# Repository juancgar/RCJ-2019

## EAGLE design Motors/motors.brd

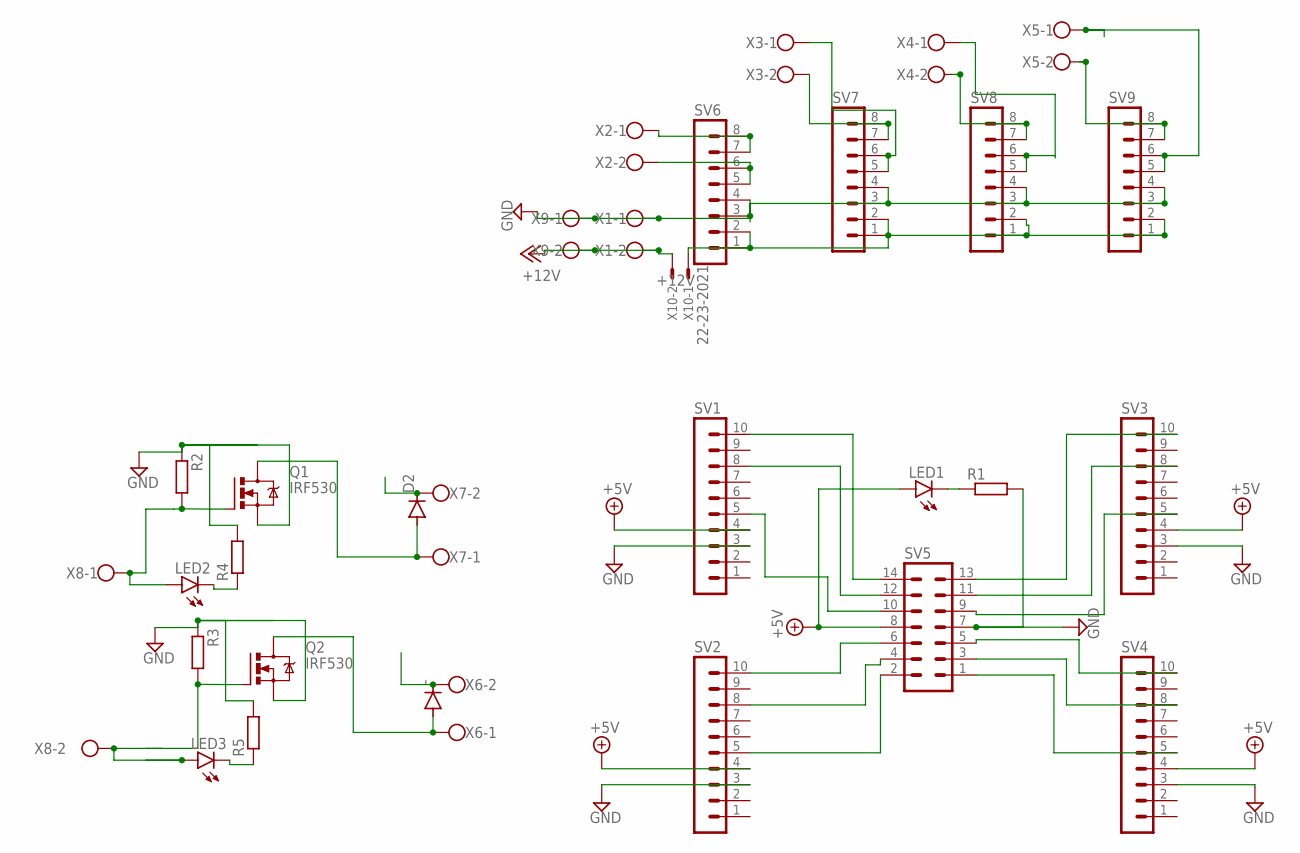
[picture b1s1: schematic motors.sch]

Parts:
-: DIODE-DO41-7.6; DO41-7.6
D2: DIODE-DO41-7.6; DO41-7.6
LED1, LED2, LED3: LED5MM
Q1, Q2: IRF530; TO220BV
R1, R2, R3, R4, R5: R-EU_0207/7; 0207/7
SV1, SV2, SV3, SV4: MA10-1
SV5: MA07-2
SV6, SV7, SV8, SV9: MA08-1
X1, X2, X3, X4, X5, X6, X7, X8, X9: W237-102
X10: 22-23-2021

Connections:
+5V: LED1.A, SV1.4, SV2.4, SV3.4, SV4.4, SV5.8
+12V: X1.2, X9.2, X10.2
GND: Q1.S, Q2.S, R1.2, R2.1, R3.1, R4.2, R5.2, SV1.3, SV2.3, SV3.3, SV4.3, SV5.7, SV6.3, SV6.4, SV7.3, SV7.4, SV8.3, SV8.4, SV9.3, SV9.4, X1.1, X9.1
unnamed: SV3.10, SV5.13
unnamed: SV3.8, SV5.11
unnamed: SV3.5, SV5.9
unnamed: SV4.10, SV5.5
unnamed: SV4.8, SV5.3
unnamed: SV4.5, SV5.1
unnamed: SV2.5, SV5.2
unnamed: SV2.8, SV5.4
unnamed: SV2.10, SV5.6
unnamed: SV1.5, SV5.10
unnamed: SV1.8, SV5.12
unnamed: SV1.10, SV5.14
unnamed: LED1.K (C), R1.1
unnamed: LED2.K (C), R4.1
unnamed: LED3.A, Q2.G, R3.2, X8.2
unnamed: D2.A, Q1.D, X7.1
unnamed: LED3.K (C), R5.1
unnamed: -.A, Q2.D, X6.1
unnamed: SV9.7, SV9.8, X5.2
unnamed: -.C, D2.C, SV6.1, SV6.2, SV7.1, SV7.2, SV8.1, SV8.2, SV9.1, SV9.2, X6.2, X7.2, X10.1
unnamed: SV6.7, SV6.8, X2.1
unnamed: SV6.5, SV6.6, X2.2
unnamed: SV7.5, SV7.6, X3.1
unnamed: SV7.7, SV7.8, X3.2
unnamed: SV8.5, SV8.6, X4.1
unnamed: LED2.A, Q1.G, R2.2, X8.1
unnamed: SV8.7, SV8.8, X4.2
unnamed: SV9.5, SV9.6, X5.1

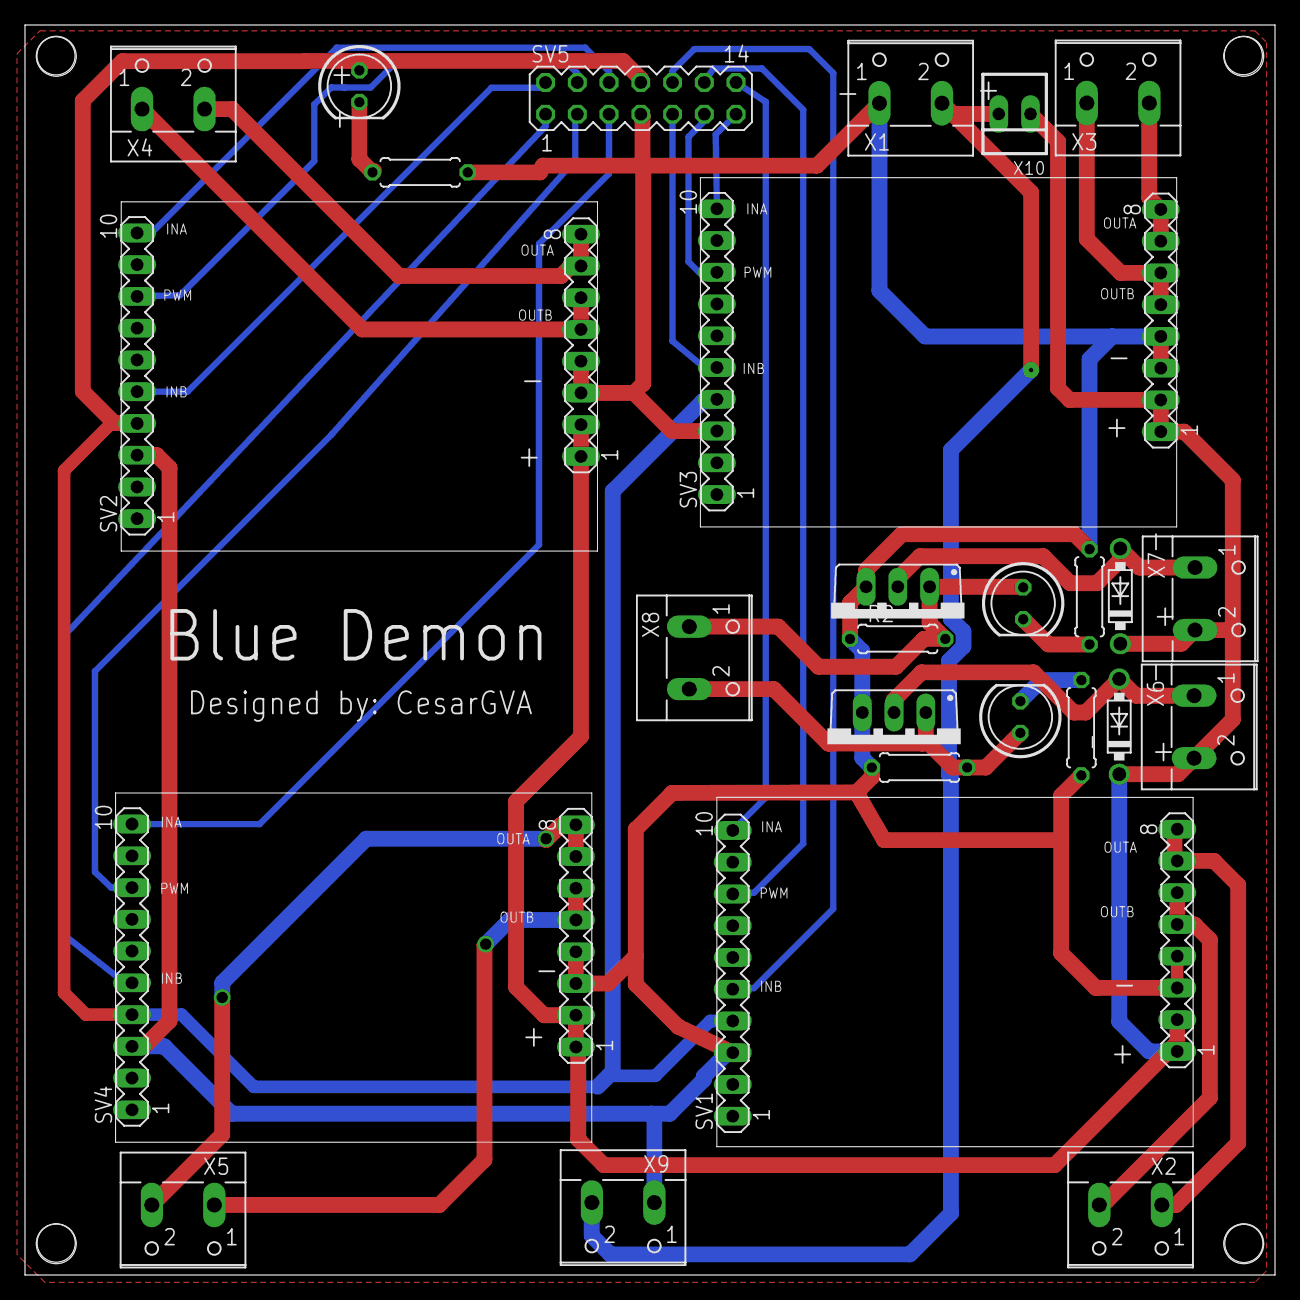
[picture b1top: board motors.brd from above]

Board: 2 copper layers, 100.0 x 100.0 mm, 31 parts (0 on the bottom side), 31 nets.

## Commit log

2019-07-02 All files
    Added all files for interview purpose
